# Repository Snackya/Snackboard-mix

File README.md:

# Snackboard µX - A DIY audio mixer for deej

## Description
The Snackboard µX (mix/myx) is a PCB to control application volumes on Linux/Windows using [deej](https://github.com/omriharel/deej).
It is powered by an Arduino Micro over USB and utilises 6 sliders to control the audio volume of the software configured in deej. The microcontroller reads the current state via a 10bit ADC and sends a value of 0-1023 to the PC and deej via serial.

The goal of this build was to create a mixer without any need for a 3D-printer, mill or any kind of casing. It takes advantage of the fact, that most PCB manufacturers only ship 5 prototype board minimum and uses one of them for part assembly and another for a faceplate. All the tracks for connecting parts are routed on the bottom copper layer, so the front paste and silk layers stay clean.

## Specifications
- 222 x 156 x 25 mm
- 6 sliders
- powered via Micro-USB
- [deej](https://github.com/omriharel/deej)

## Parts
- 1x Arduino Micro
- 6x Alps sliding potentiometers, linear, RSA0N12-LIN10K (most alps sliders should work. make sure they are linear and have the same footprint)
- 5x M4 bolts
- 20x M4 nuts

## Usage
Just submit the files in /gerber/ to your preferred PCB manufacturer. (Most manufacturers prefer a .zip archive of these files.)

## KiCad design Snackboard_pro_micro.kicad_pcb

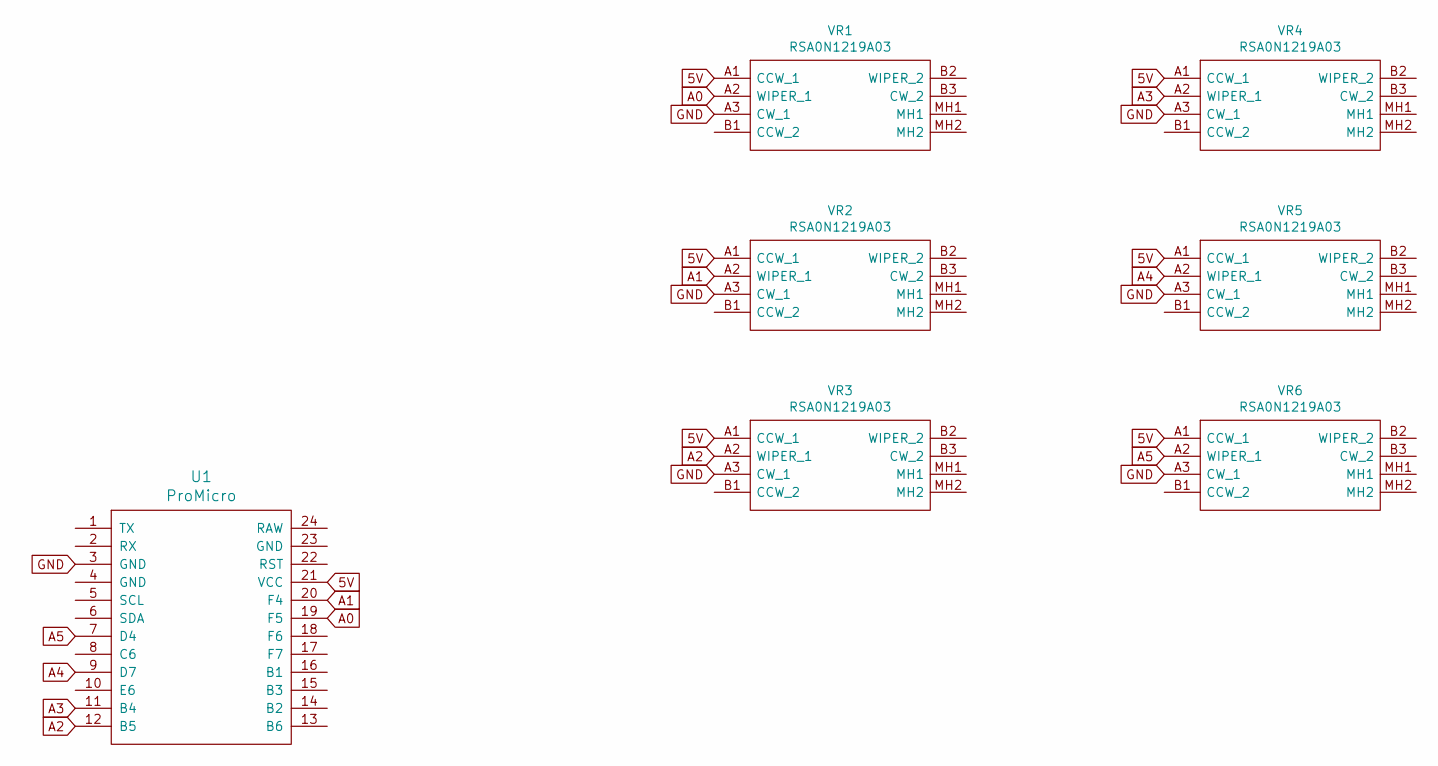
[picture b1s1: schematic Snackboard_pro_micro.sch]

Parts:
U1: ProMicro
VR1, VR2, VR3, VR4, VR5, VR6: RSA0N1219A03; Mouser Part Number 688-RSA0N1219A03

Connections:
5V: U1.21 (VCC), VR1.A1 (CCW_1), VR2.A1 (CCW_1), VR3.A1 (CCW_1), VR4.A1 (CCW_1), VR5.A1 (CCW_1), VR6.A1 (CCW_1)
A0: U1.19 (F5), VR1.A2 (WIPER_1)
A1: U1.20 (F4), VR2.A2 (WIPER_1)
A2: U1.12 (B5), VR3.A2 (WIPER_1)
A3: U1.11 (B4), VR4.A2 (WIPER_1)
A4: U1.9 (D7), VR5.A2 (WIPER_1)
A5: U1.7 (D4), VR6.A2 (WIPER_1)
GND: U1.3 (GND), VR1.A3 (CW_1), VR2.A3 (CW_1), VR3.A3 (CW_1), VR4.A3 (CW_1), VR5.A3 (CW_1), VR6.A3 (CW_1)

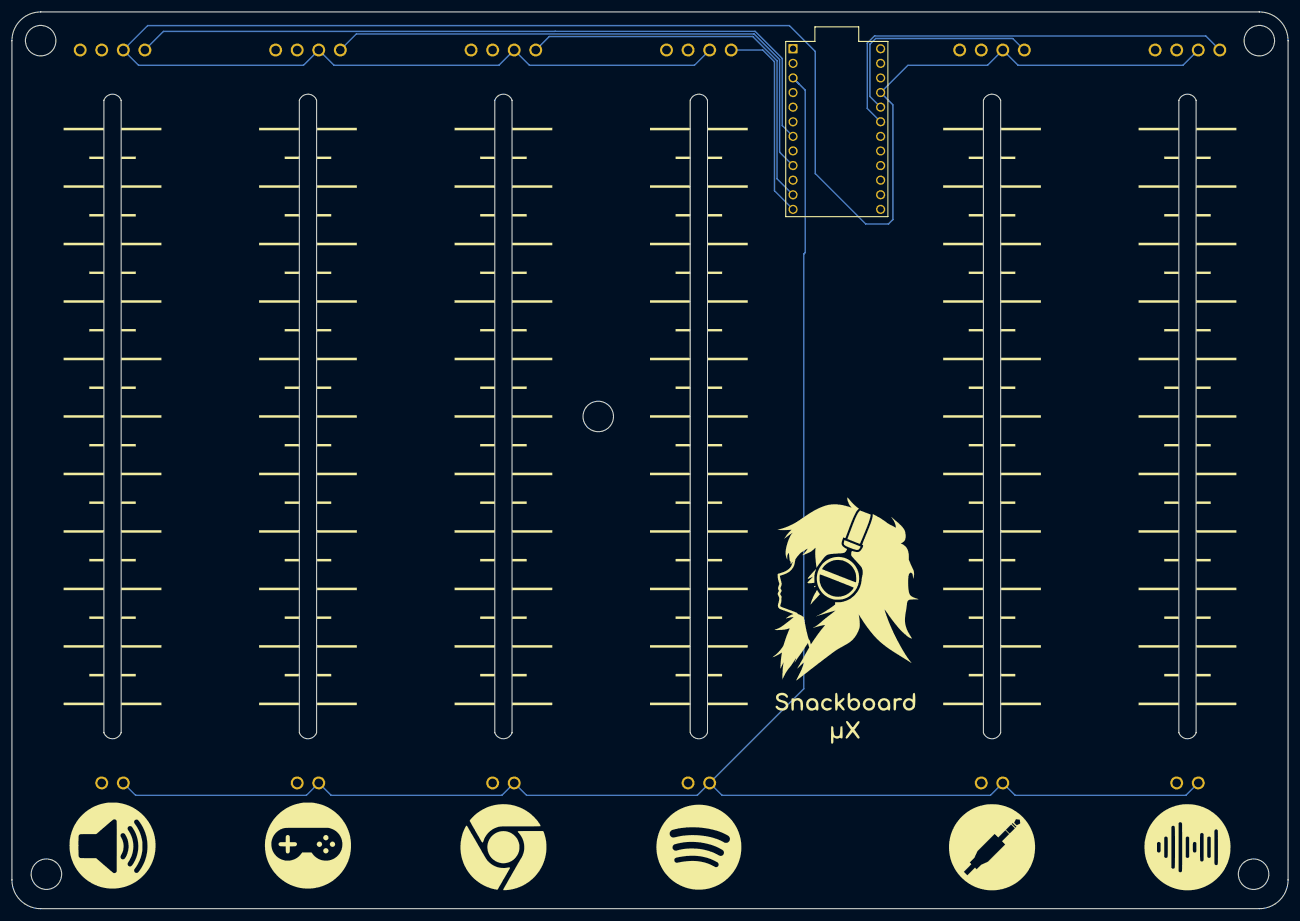
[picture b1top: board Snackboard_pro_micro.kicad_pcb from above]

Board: 2 copper layers, 222.0 x 156.0 mm, 7 parts (0 on the bottom side), 8 nets.

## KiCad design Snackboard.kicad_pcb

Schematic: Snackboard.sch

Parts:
VR1, VR2, VR3, VR4, VR5, VR6: RSA0N1219A03; Mouser Part Number 688-RSA0N1219A03
XA1: Arduino_Micro_Socket

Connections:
5V: VR1.A1 (CCW_1), VR2.A1 (CCW_1), VR3.A1 (CCW_1), VR4.A1 (CCW_1), VR5.A1 (CCW_1), VR6.A1 (CCW_1), XA1.5V
A0: VR1.A2 (WIPER_1), XA1.A0
A1: VR2.A2 (WIPER_1), XA1.A1
A2: VR6.A2 (WIPER_1), XA1.A2
A3: VR5.A2 (WIPER_1), XA1.A3
A4: VR4.A2 (WIPER_1), XA1.A4
A5: VR3.A2 (WIPER_1), XA1.A5
GND: VR1.A3 (CW_1), VR2.A3 (CW_1), VR3.A3 (CW_1), VR4.A3 (CW_1), VR5.A3 (CW_1), VR6.A3 (CW_1), XA1.GND1

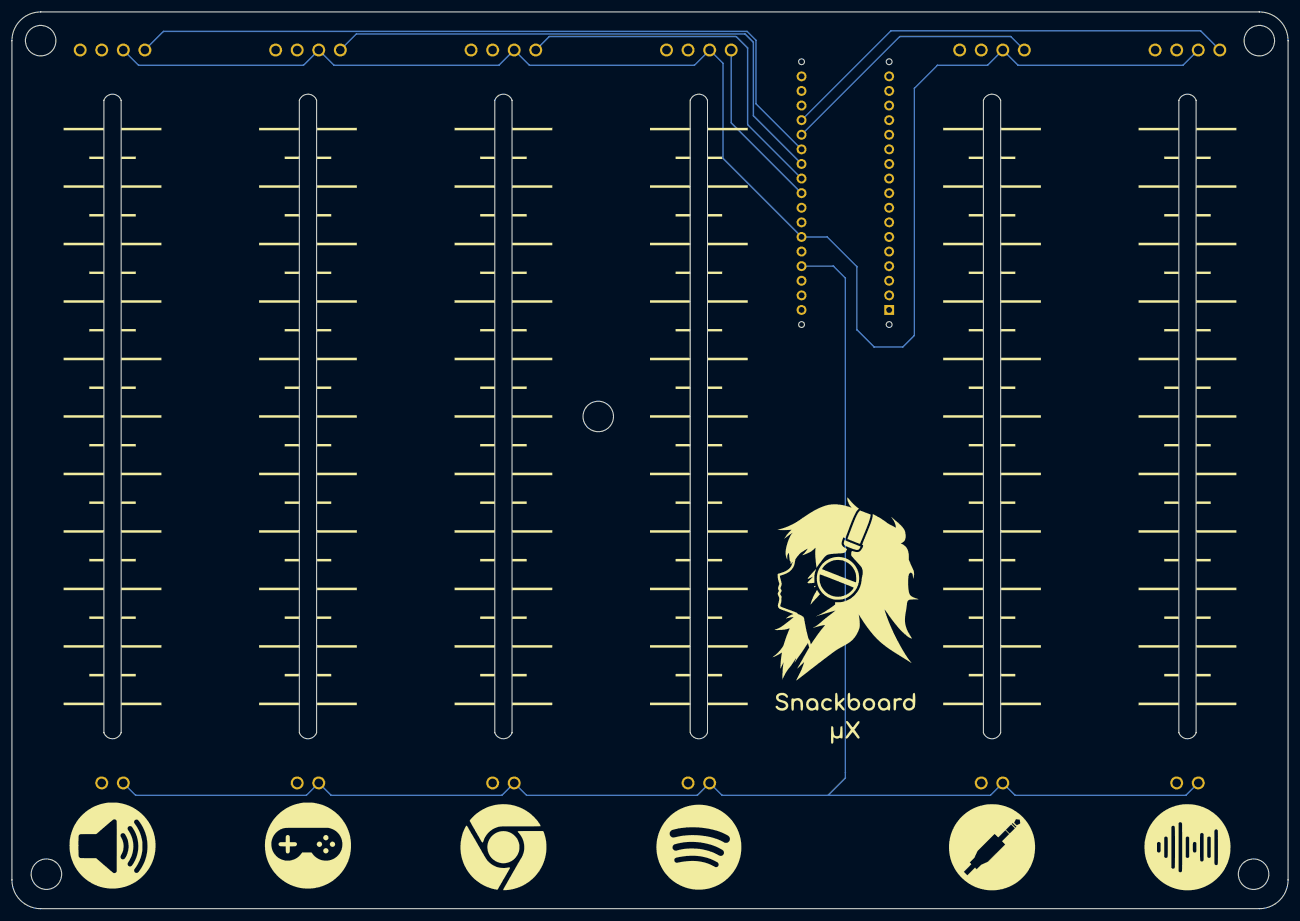
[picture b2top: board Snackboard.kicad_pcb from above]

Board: 2 copper layers, 222.0 x 156.0 mm, 7 parts (0 on the bottom side), 8 nets.

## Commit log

2020-06-16 Add project files
    added schematic, gerber files and photos
2020-07-07 Update README.md
    changed parts description, since the Pro version of the Arduino Micro available in overseas retail seems to have a different pinout
2020-07-07 add pro micro version
    - deleted gerber files for paste, since it was unused
    - changed folder structure
2022-07-14 add gitignore
2022-07-14 add KiCAD project files
2022-07-14 reduce img file size
2022-07-14 edit lib directory
